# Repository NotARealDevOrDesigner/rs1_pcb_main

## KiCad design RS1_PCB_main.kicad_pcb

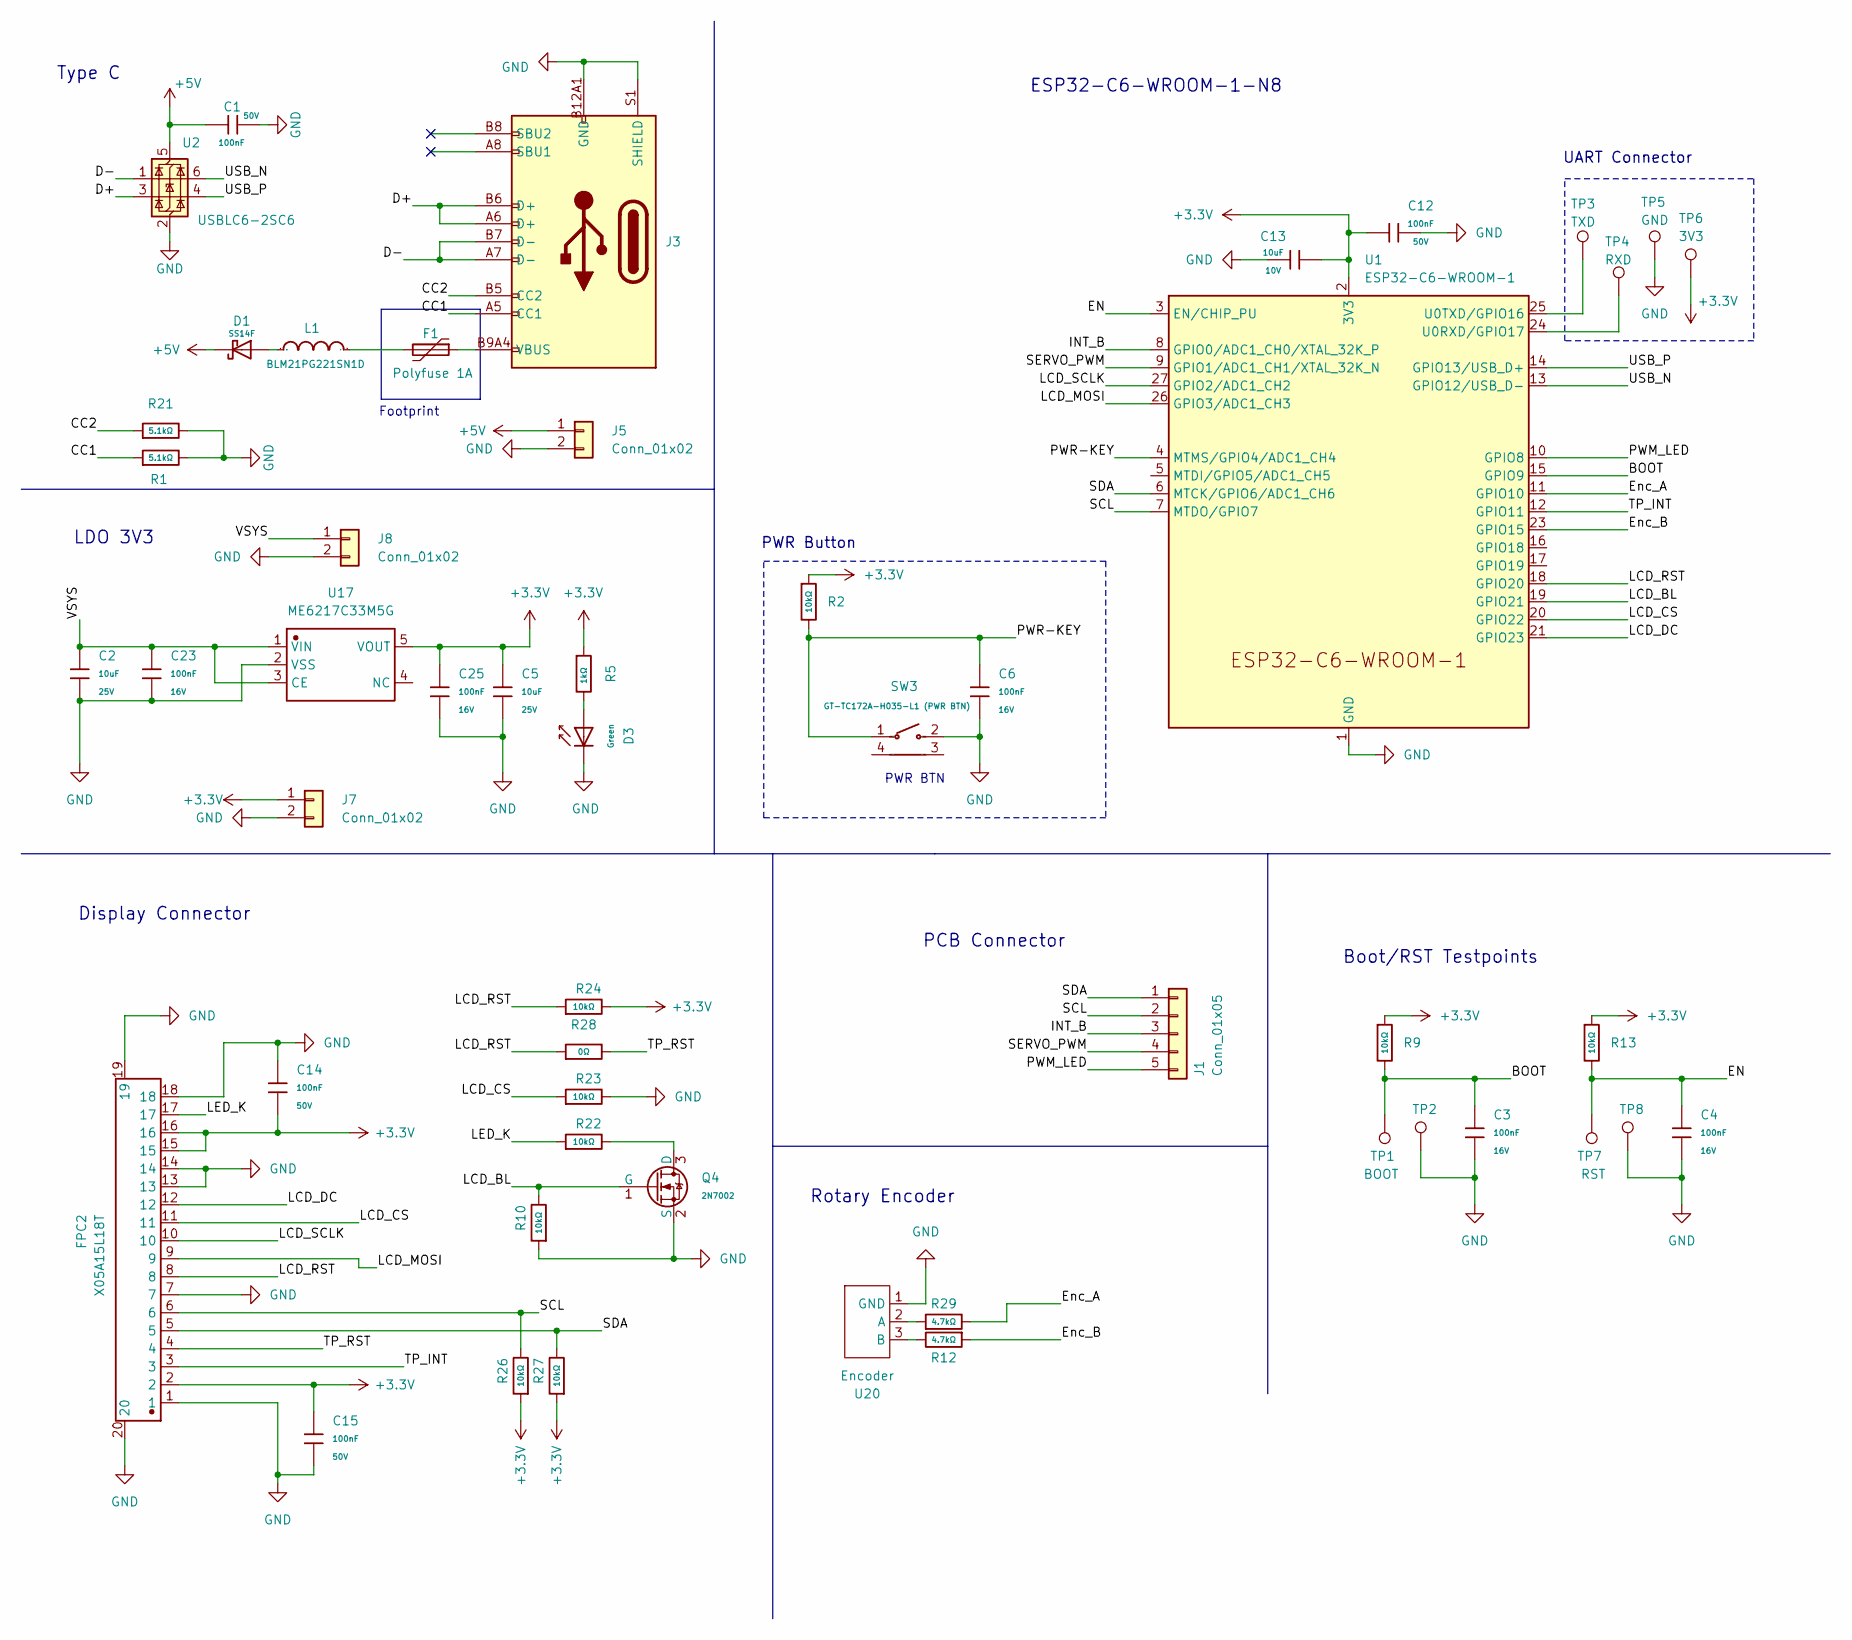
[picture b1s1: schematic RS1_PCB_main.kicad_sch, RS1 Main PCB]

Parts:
C1, C12, C14, C15: 100nF; C_0603; Voltage Rated 50V; Tolerance ±10%; Part CC0603KRX7R9BB104; LCSC C14663
C2, C5: 10uF; C_0805; Voltage Rated 25V; Tolerance ±10%; Part CL21A106KAYNNNE; LCSC C15850
C3, C4, C6, C23, C25: 100nF; C_0402; Voltage Rated 16V; Tolerance ±10%; Part CL05B104KO5NNNC; LCSC C1525
C13: 10uF; C_0603; Voltage Rated 10V; Tolerance ±10%; Part CL10A106KP8NNNC; LCSC C19702
D1: SS14F; D_SMAF; Forward Voltage (Vf@If) 550mV@1.0A; Reverse Voltage (Vr) 40V; Part SS14F; LCSC C18199203
D3: Green; D_0805; Part KT-0805G; LCSC C2297
F1: Polyfuse 1A; Fuse_1206_3216Metric
FPC2: X05A15L18T; FPC-SMD_18P-P0.50_ZX-0.5FPC-2H-HFJ18P; Manufacturer Part X05A15L18T
J1: Conn_01x05; PinHeader_1x05_P2.54mm_Vertical_SMD_Pin1Right
J3: Connector, USB-TYPE-C-16P; TYPE-C-SMD_HX-TYPE-C-16PIN; LCSC C2927039
J5, J7, J8: Conn_01x02; PinHeader_1x02_P2.54mm_Vertical
L1: BLM21PG221SN1D; L0805; Manufacturer Part BLM21PG221SN1D
Q4: 2N7002; Q_SOT-23; Part 2N7002; LCSC C8545
R1, R21: 5.1kΩ; R_0402; Overload Voltage (Max) 50V; Tolerance ±1%; Part 0402WGF5101TCE; LCSC C25905
R2: 10kΩ; R_0603; Overload Voltage (Max) 75V; Tolerance ±1%; Part 0603WAF1002T5E; LCSC C25804
R5: 1kΩ; R_0603; Overload Voltage (Max) 75V; Tolerance ±1%; Part 0603WAF1001T5E; LCSC C21190
R9, R10, R13, R22, R23, R24, R26, R27: 10kΩ; R_0402; Overload Voltage (Max) 50V; Tolerance ±1%; Part 0402WGF1002TCE; LCSC C25744
R12, R29: 4.7kΩ; R_0402; Overload Voltage (Max) 50V; Tolerance ±1%; Part 0402WGF4701TCE; LCSC C25900
R28: 0Ω; R_0805; Overload Voltage (Max) 150V; Tolerance ±1%; Part 0805W8F0000T5E; LCSC C17477
SW3: GT-TC172A-H035-L1 (PWR BTN); SW-SMD_GT-TC172A-H035-L1; Manufacturer Part GT-TC172A-H035-L1
TP1: BOOT; TestPoint_Pad_D1.5mm
TP2, TP8: -; TestPoint_Pad_D1.5mm
TP3: TXD; TestPoint_Pad_D1.5mm
TP4: RXD; TestPoint_Pad_D1.5mm
TP5: GND; TestPoint_Pad_D1.5mm
TP6: 3V3; TestPoint_Pad_D1.5mm
TP7: RST; TestPoint_Pad_D1.5mm
U1: ESP32-C6-WROOM-1
U2: USBLC6-2SC6; SOT-23-6
U17: ME6217C33M5G; SOT-23-5_L3.0-W1.7-P0.95-LS2.8-BR; Manufacturer Part ME6217C33M5G
U20: Encoder; Encoder_Connector_Pads

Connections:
+3.3V: C5.1, C12.1, C13.2, C14.2, C15.1, C25.1, FPC2.2, FPC2.15, FPC2.16, J7.1, R2.1, R5.1, R9.1, R13.1, R24.2, R26.1, R27.1, TP6.1, U1.2 (3V3), U17.5 (VOUT)
+5V: C1.1, D1.1, J5.1, U2.5 (VBUS)
/BOOT: C3.1, R9.2, TP1.1, U1.15 (GPIO9)
/CC1: J3.A5 (CC1), R1.1
/CC2: J3.B5 (CC2), R21.1
/D+: J3.A6 (D+), J3.B6 (D+), U2.3 (I/O2)
/D-: J3.A7 (D-), J3.B7 (D-), U2.1 (I/O1)
/EN: C4.1, R13.2, TP7.1, U1.3 (EN/CHIP_PU)
/Enc_A: R29.2, U1.11 (GPIO10)
/Enc_B: R12.1, U1.23 (GPIO15)
/INT_B: J1.3, U1.8 (GPIO0/ADC1_CH0/XTAL_32K_P)
/LCD_BL: Q4.1 (G), R10.2, U1.19 (GPIO21)
/LCD_CS: FPC2.11, R23.1, U1.20 (GPIO22)
/LCD_DC: FPC2.12, U1.21 (GPIO23)
/LCD_MOSI: FPC2.9, U1.26 (GPIO3/ADC1_CH3)
/LCD_RST: FPC2.8, R24.1, R28.1, U1.18 (GPIO20)
/LCD_SCLK: FPC2.10, U1.27 (GPIO2/ADC1_CH2)
/LED_K: FPC2.17, R22.1
/PWM_LED: J1.5, U1.10 (GPIO8)
/PWR-KEY: C6.1, R2.2, SW3.1, U1.4 (MTMS/GPIO4/ADC1_CH4)
/SCL: FPC2.6, J1.2, R26.2, U1.7 (MTDO/GPIO7)
/SDA: FPC2.5, J1.1, R27.2, U1.6 (MTCK/GPIO6/ADC1_CH6)
/SERVO_PWM: J1.4, U1.9 (GPIO1/ADC1_CH1/XTAL_32K_N)
/TP_INT: FPC2.3, U1.12 (GPIO11)
/TP_RST: FPC2.4, R28.2
/USB_N: U1.13 (GPIO12/USB_D-), U2.6 (I/O1)
/USB_P: U1.14 (GPIO13/USB_D+), U2.4 (I/O2)
/VSYS: C2.1, C23.1, J8.1, U17.1 (VIN), U17.3 (CE)
GND: C1.2, C2.2, C3.2, C4.2, C5.2, C6.2, C12.2, C13.1, C14.1, C15.2, C23.2, C25.2, D3.1, FPC2.1, FPC2.7, FPC2.13, FPC2.14, FPC2.18, FPC2.19, FPC2.20, J3.A12B1 (GND), J3.B12A1 (GND), J3.S1 (SHIELD), J5.2, J7.2, J8.2, Q4.2 (S), R1.2, R10.1, R21.2, R23.2, SW3.2, TP2.1, TP5.1, TP8.1, U1.1 (GND), U1.28 (GND), U1.29 (GND), U2.2 (GND), U17.2 (VSS), U20.1 (GND)
unnamed: D1.2, L1.1
unnamed: D3.2, R5.2
unnamed: F1.1, J3.A9B4 (VBUS), J3.B9A4 (VBUS)
unnamed: F1.2, L1.2
unnamed: Q4.3 (D), R22.2
unnamed: TP4.1, U1.24 (U0RXD/GPIO17)
unnamed: TP3.1, U1.25 (U0TXD/GPIO16)
unnamed: R29.1, U20.2 (A)
unnamed: R12.2, U20.3 (B)

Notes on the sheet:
Rotary Encoder
Type C
ESP32-C6-WROOM-1-N8
LDO 3V3
Boot/RST Testpoints
Display Connector
UART Connector
Footprint
PWR BTN
PCB Connector
PWR Button

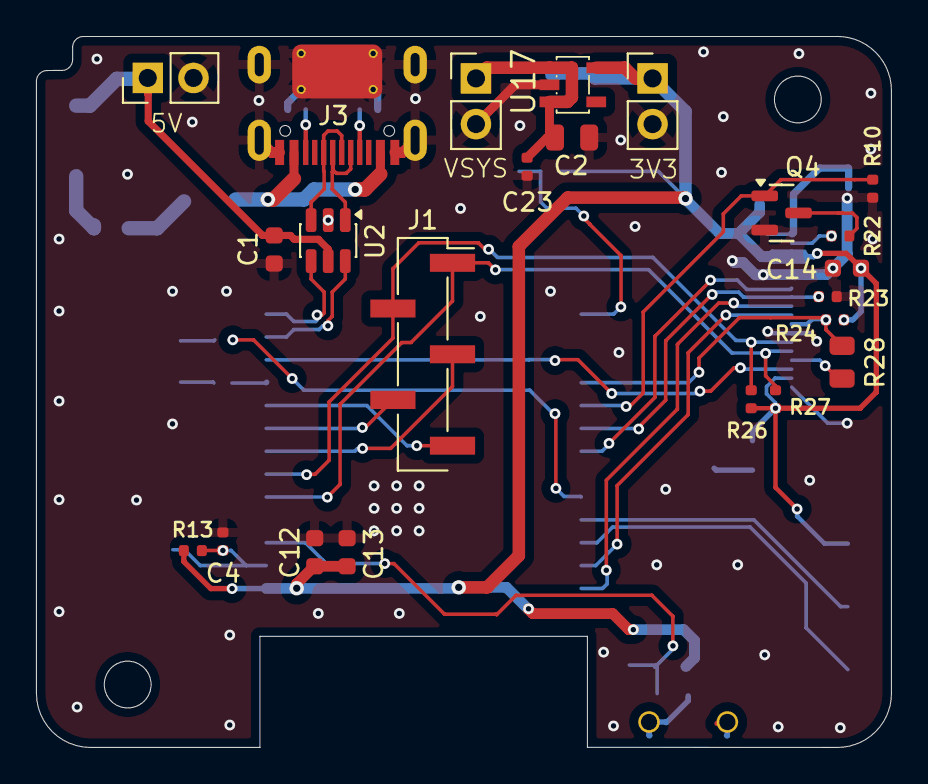
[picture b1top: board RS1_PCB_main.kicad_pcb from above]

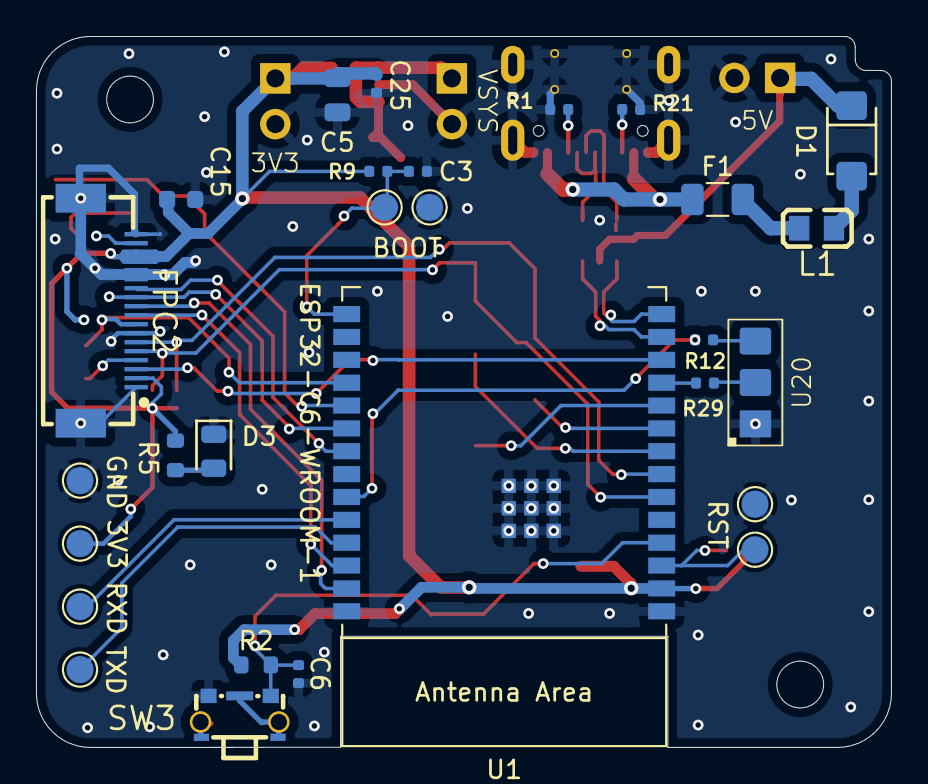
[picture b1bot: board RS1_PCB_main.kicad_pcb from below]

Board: 2 copper layers, 47.5 x 39.5 mm, 51 parts (28 on the bottom side), 38 nets.

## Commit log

2026-01-13 init commit
2026-01-14 changed layout
2026-01-16 changed layout (position ldo, pins...)
2026-01-16 all connected
2026-01-16 changed testpoints, worked on silkprints
2026-01-16 fixed hole position and touchingpoints of housing
2026-01-16 small adj
2026-01-17 switch commit
